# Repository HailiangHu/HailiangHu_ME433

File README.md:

Name: Hailiang Hu
Date: 2016/4/1
For ME433 project
Another line added

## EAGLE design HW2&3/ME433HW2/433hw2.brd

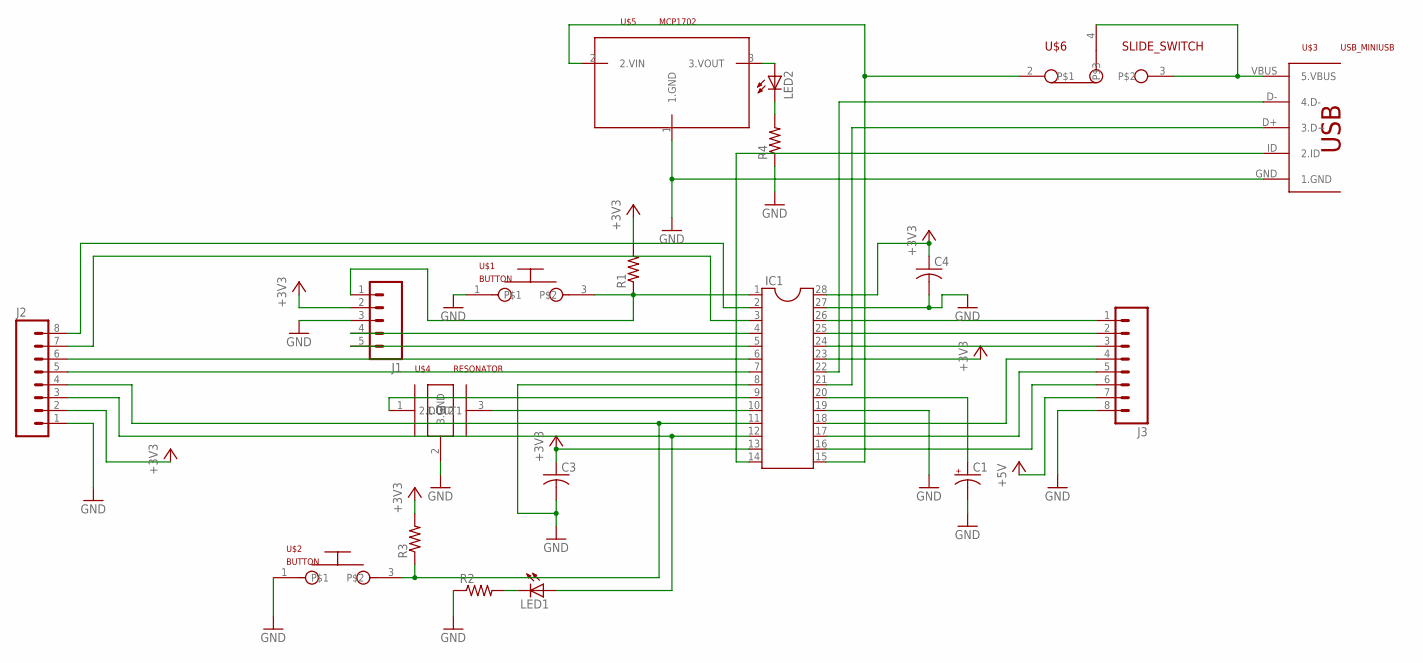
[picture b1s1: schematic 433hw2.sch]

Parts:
C1: CPOL-USE2.5-6; E2,5-6
C3, C4: C-US025-025X050; C025-025X050
IC1: DIL28-4
J1: M05PTH; 1X05
J2, J3: M08; 1X08_ROUND
LED1, LED2: LED3MM
R1, R2, R3, R4: R-US_0207/7; 0207/7
U$1, U$2: BUTTON
U$3: USB_MINIUSB; USB-MB-H
U$4: RESONATOR; 1X03
U$5: MCP1702; TO92
U$6: SLIDE_SWITCH; 1X05

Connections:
+3V3: C3.1, C4.1, IC1.13, IC1.23, IC1.28, J1.2, J2.2, R1.2, R3.2
+5V: J3.7
GND: C1.-, C3.2, C4.2, IC1.8, IC1.19, IC1.27, J1.3, J2.1, J3.8, R2.1, R4.1, U$1.1, U$2.1, U$3.GND (1.GND), U$4.2 (3.GND), U$5.1 (1.GND)
unnamed: IC1.1, J1.1, R1.1, U$1.3
unnamed: IC1.10, U$4.3 (2.OUT2)
unnamed: IC1.9, U$4.1 (1.OUT1)
unnamed: IC1.5, J1.5
unnamed: LED1.K (C), R2.2
unnamed: IC1.12, J2.3, LED1.A
unnamed: IC1.4, J1.4
unnamed: LED2.A, U$5.3 (3.VOUT)
unnamed: LED2.K (C), R4.2
unnamed: IC1.15, U$5.2 (2.VIN), U$6.2
unnamed: C1.+, IC1.20
unnamed: IC1.14, U$3.ID (2.ID)
unnamed: IC1.22, U$3.D- (4.D-)
unnamed: IC1.21, U$3.D+ (3.D+)
unnamed: IC1.2, J2.8
unnamed: IC1.26, J3.1
unnamed: IC1.11, J2.4, R3.1, U$2.3
unnamed: IC1.3, J2.7
unnamed: IC1.6, J2.6
unnamed: IC1.7, J2.5
unnamed: IC1.25, J3.2
unnamed: IC1.24, J3.3
unnamed: IC1.18, J3.4
unnamed: IC1.17, J3.5
unnamed: IC1.16, J3.6
unnamed: U$3.VBUS (5.VBUS), U$6.3, U$6.4

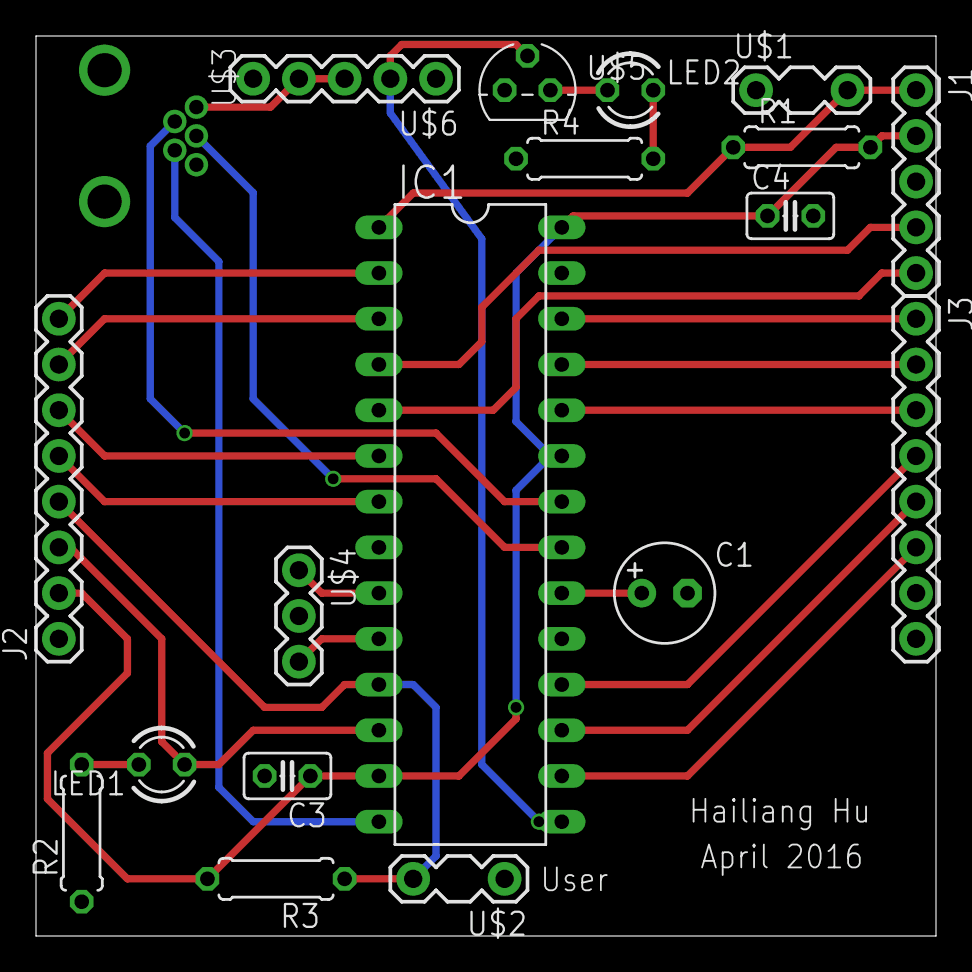
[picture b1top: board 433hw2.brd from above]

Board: 2 copper layers, 50.0 x 50.0 mm, 19 parts (0 on the bottom side), 28 nets.

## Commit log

2016-04-01 :lollipop: Added .gitattributes & .gitignore files
2016-04-01 add a line
2016-04-02 code template downloaded
2016-04-02 initial main.c
2016-04-02 config
2016-04-04 monday
2016-04-04 led output 1000Hz
2016-04-04 comment added
2016-04-05 Add circuit
2016-04-07 LIBS
2016-04-09 USB_MBH
2016-04-10 SCHEMATIC
2016-04-10 layout1
2016-04-10 layout
2016-04-13 new_layout
2016-04-13 Gerber files
    Ready to be checked before order
2016-04-18 SPI-dac
2016-04-21 spi output square wave
2016-04-21 dac output sine
2016-04-21 spi dac output sin and triangle wave
2016-05-25 spi_dac_photo
2016-05-25 I2C_expander_photo
2016-05-29 Lcd end
2016-06-05 motor
